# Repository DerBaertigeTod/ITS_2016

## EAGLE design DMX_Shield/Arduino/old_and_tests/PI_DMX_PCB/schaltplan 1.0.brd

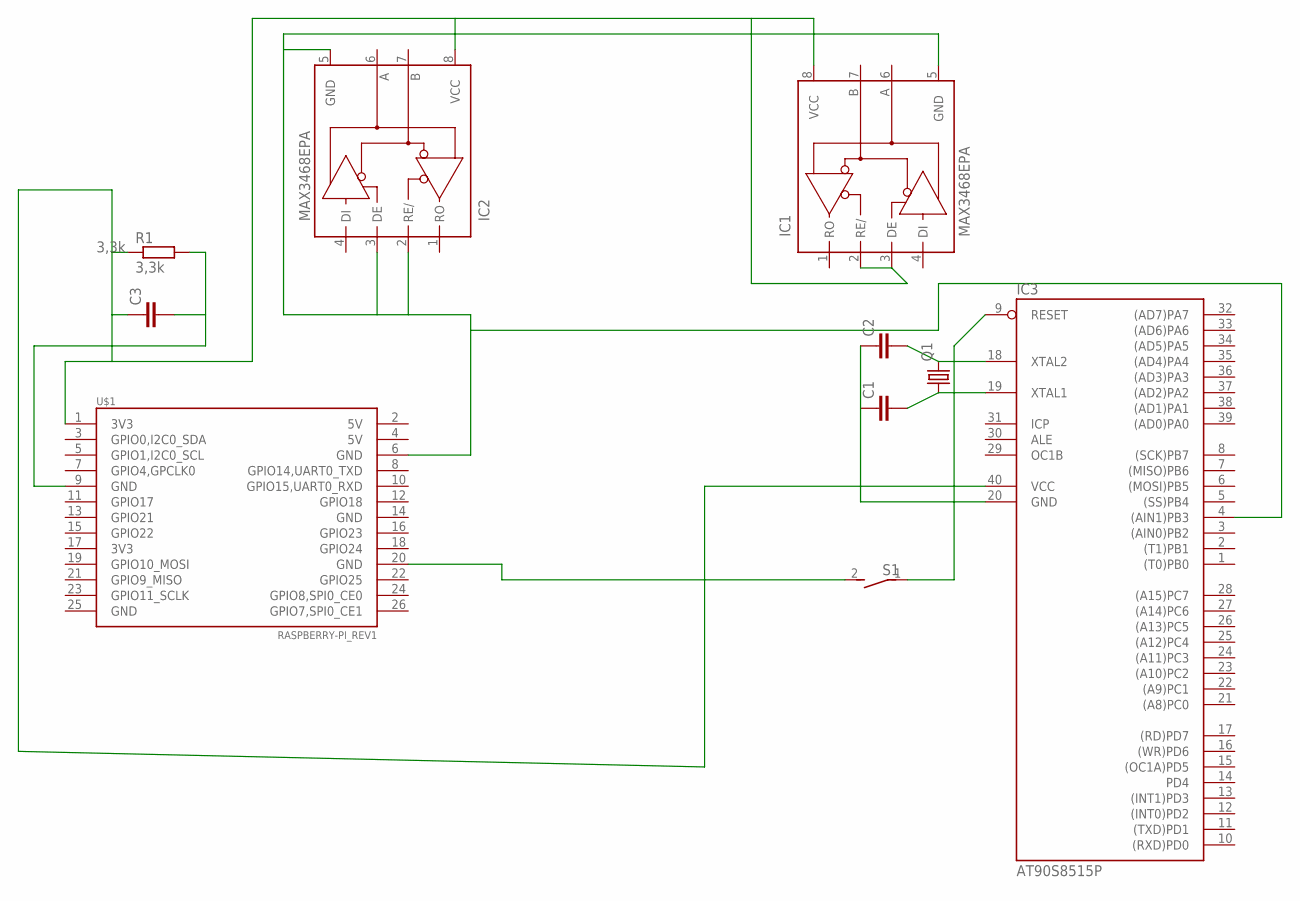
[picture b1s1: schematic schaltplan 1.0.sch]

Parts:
C1, C2, C3: C2.5/5; C2.5-5
IC1, IC2: MAX3468EPA; DIL08
IC3: AT90S8515P; DIL40
Q1: CRYSTALHC49U-V; HC49U-V
R1: 3,3k; 0204/7
S1: DS01E; DS-01
U$1: RASPBERRY-PI_REV1

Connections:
unnamed: C3.1, IC1.2 (RE/), IC1.3 (DE), IC1.8 (VCC), IC2.8 (VCC), IC3.40 (VCC), R1.1, U$1.1 (3V3)
unnamed: C3.2, R1.2, U$1.9 (GND)
unnamed: C1.2, IC3.19 (XTAL1), Q1.1
unnamed: C2.2, IC3.18 (XTAL2), Q1.2
unnamed: C1.1, C2.1, IC3.20 (GND)
unnamed: IC1.5 (GND), IC2.2 (RE/), IC2.3 (DE), IC2.5 (GND), IC3.4 ((AIN1)PB3), U$1.6 (GND)
unnamed: IC3.9 (RESET), S1.1
unnamed: S1.2, U$1.20 (GND)

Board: 2 copper layers, 10 parts (0 on the bottom side), 8 nets, no tracks yet.

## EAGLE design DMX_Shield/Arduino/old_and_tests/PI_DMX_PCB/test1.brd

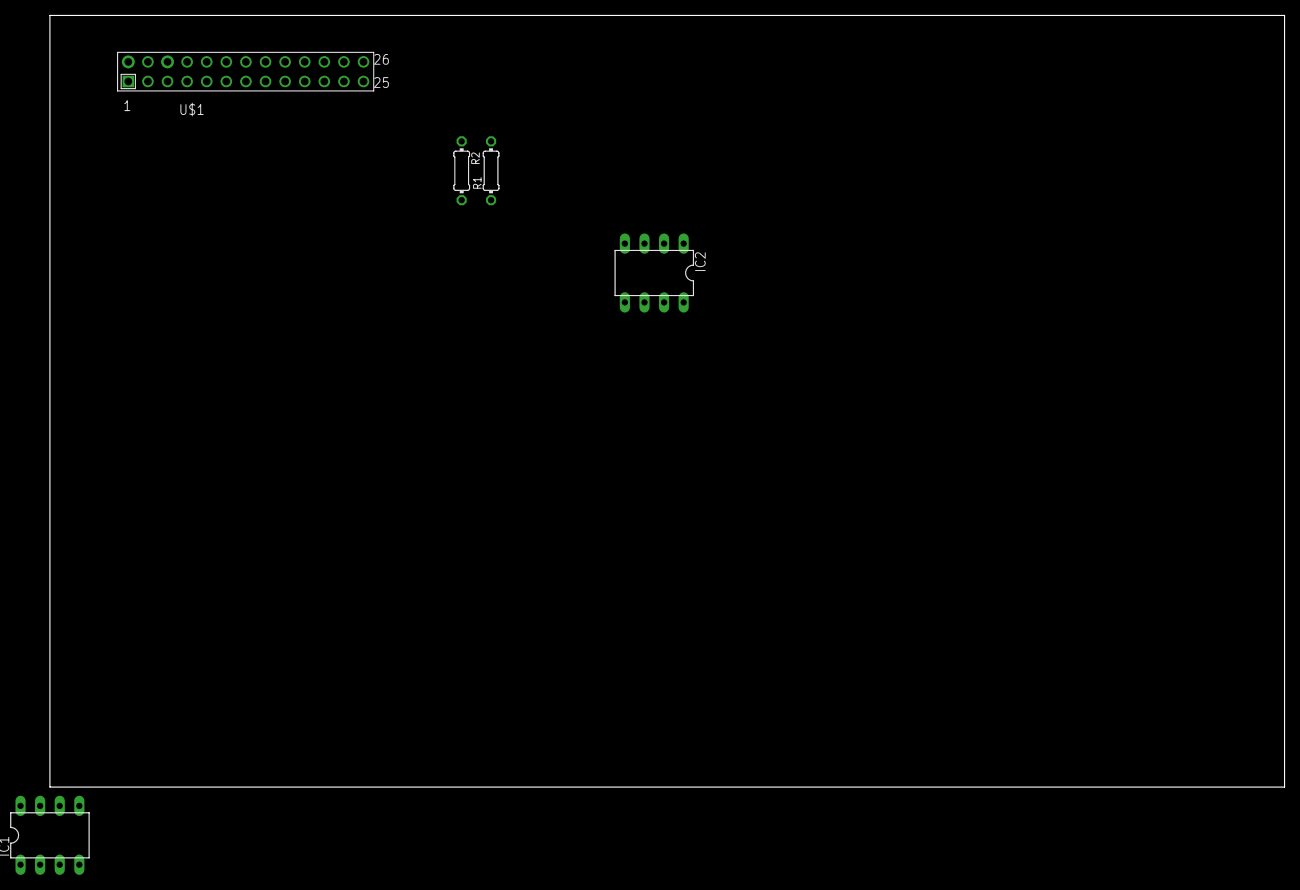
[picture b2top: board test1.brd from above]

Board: 2 copper layers, 160.0 x 100.0 mm, 5 parts (0 on the bottom side), 2 nets, no tracks yet.

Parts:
IC1, IC2: MAX3468EPA; DIL08
R1: 3,3k; 0204/7
R2: 1,6k; 0204/7
U$1: RASPBERRY-PI_REV1

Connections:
GND: IC1.5, IC2.5
VCC: IC1.8, IC2.8

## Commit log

2016-05-26 :tada: Added .gitattributes & .gitignore files
2016-05-26 copy
    aus dropbox kopiert
2016-05-26 Scripts von Axel
2016-05-26 DMX_Schaltplan & EAGLE FILES
2016-05-26 html code von Kai & Neuer Arduino Sketch
2016-05-26 I2c raus & 1 socket test
2016-05-26 ahhhhhhh
2016-05-26 Revert "I2c raus & 1 socket test"
    This reverts commit 6765d041006ba268388d19f5baf786a9d288cb26.
2016-05-26 blubbbbb
2016-05-26 funzt,
    aber böse timingprobleme
2016-05-27 working state 1 ALPHA
    Alle timeouts rausgeworfen
    Scripte vom Pi übernommen
2016-05-27 checkbox_app
    vergessen die checkbox app zu adden
2016-05-27 new test app, sends & receive "NOT TESTED!"
    can send data setted by slider and checkbox pushes values
    receives data every 1.5 sec
2016-05-27 typo
2016-05-31 Name geändert
    Neue Paketbeschreibung
2016-06-16 Initial Release ^^
2016-06-16 test rgbw dmx return
2016-06-16 console log
2016-06-16 nochmal test
2016-06-16 könnte laufen
2016-06-16 fehler in color for preview
2016-06-16 default values
2016-06-16 neues default variables
2016-06-16 buttons display none
    erstmal nicht mehr benötigt
2016-06-16 vector calc for color
2016-06-16 color backup
2016-06-16 hintergrund und schrift farbe geändert
2016-06-20 new ardu sctech with complete conceptionetics
2016-06-20 Fritzing
2016-06-20 DMX_Board Firmware
2016-06-20 fritzing schoen
    kein vcc auf ground
2016-06-20 leiterbahn update
    auch kein ground auf vcc
2016-06-21 dmx wire
    jetzt auch mit senden
2016-06-21 next try
    ss und reset switch
2016-06-21 new firmware
2016-06-21 without slave
2016-06-21 test firmwares
2016-06-21 Musiktitel Lauftext + Hintergrundfarbe ändert sich
2016-06-21 blink test
2016-06-21 nochmal in schoen
    schaltplan in schoen
2016-06-21 Revert "next try"
    This reverts commit 5cd14370a20b2228155b0b8f6611850bff6b7e00.
2016-06-21 new blink
2016-06-21 new test
2016-06-21 new blink test
2016-06-22 hoffentlich das letzte mal
    c3 und r3 dazu
2016-06-22 makeup
    letzte kleine Aenderungen
2016-06-24 new arduino sctech for ATmega162
2016-06-24 some changes
2016-06-24 threading
2016-06-24 last_received init
2016-06-24 new ardu scetch and debug code
2016-06-27 eagle library
2016-06-27 dbhandler
2016-06-27 db handler gesocketed :+1:
2016-06-27 python shell raus
2016-06-27 Interpret / Title Anzeige, Like / Dislike Emit
2016-06-27 Klammern in app.js vergesse
2016-06-27 Like / Dislike Counter RAAAAUS
2016-06-27 leiterplatte
    oszie und max und mega
    und iwie anderer kram
2016-07-13 aufräumen
    MUSIC IS NOT INCLUDED!!!
2016-07-13 clean up
2016-07-13 schaltplan ohne ss
    schaltplan stand von der ausstelung
2016-07-13 Bilder, Plakat, Doku
    ein paar mbs mehr :dancers:
2016-07-13 doku finish
